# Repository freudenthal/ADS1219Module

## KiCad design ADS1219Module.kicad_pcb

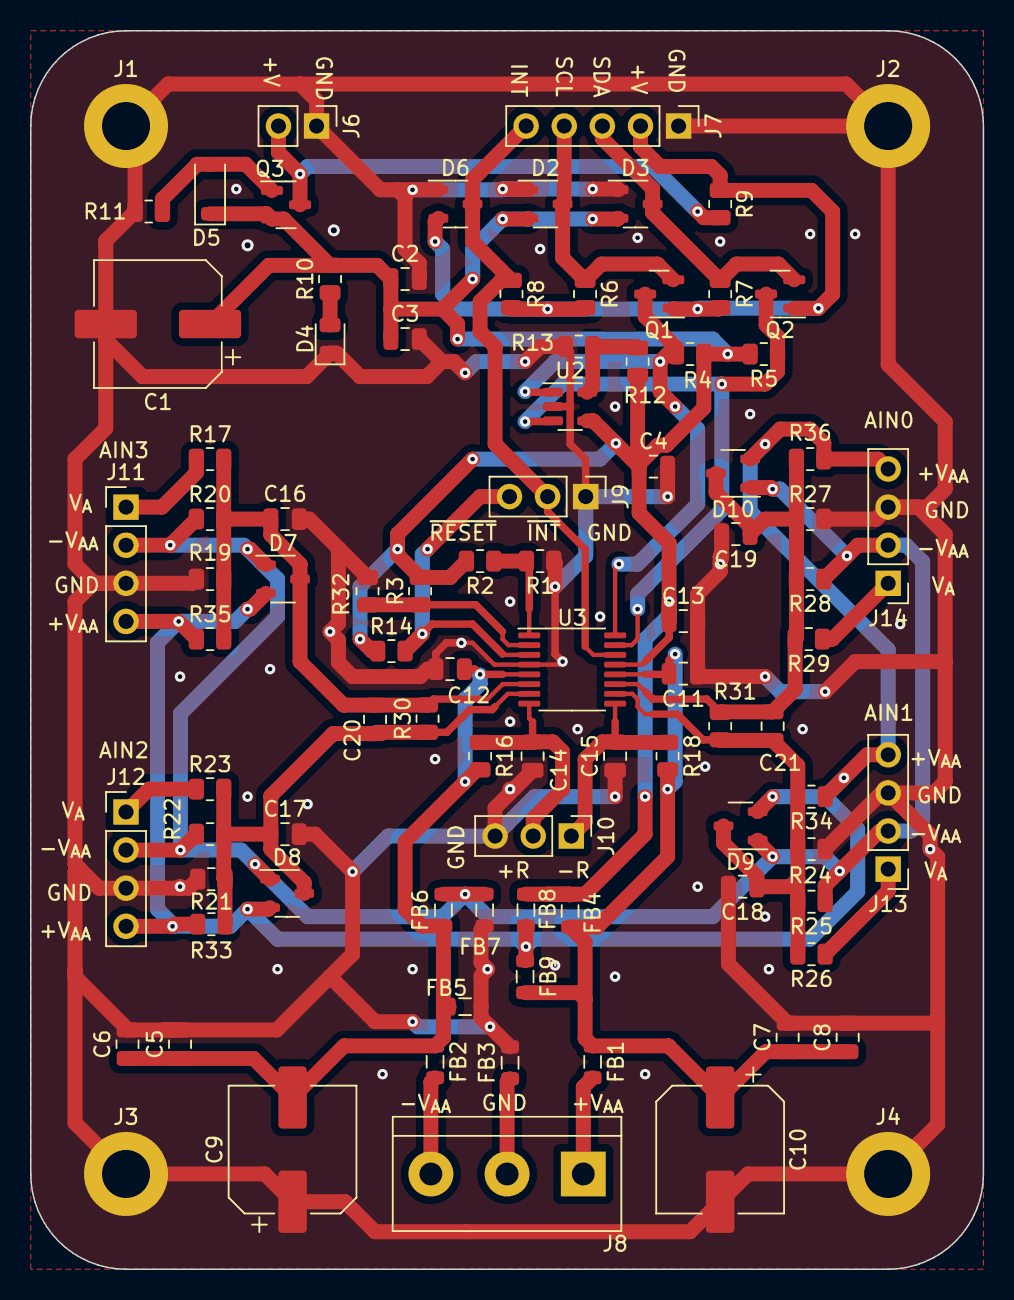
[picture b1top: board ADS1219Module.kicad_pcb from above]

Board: 2 copper layers, 63.5 x 82.5 mm, 92 parts (0 on the bottom side), 32 nets.

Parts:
C1, C9, C10: 100uF; CP_Elec_8x11.9
C2, C6, C8: 10uF; C_0805_2012Metric
C3, C4, C5, C7, C11, C12, C13, C14, C15, C16, C17, C18, C19: 1uF; C_0805_2012Metric
C20, C21: NSF; C_0805_2012Metric
D2, D3, D6, D7, D8, D9, D10: 100V; SOT-23-3
D4: LED; LED_0805_2012Metric
D5: 10V; D_SOD-123
FB1, FB2, FB3: FerriteBead; L_0805_2012Metric
FB4, FB5, FB6, FB7, FB8, FB9: NS_Ferrite; L_0805_2012Metric
J1, J2, J3, J4: M3; MountingHole_3.2mm_M3_DIN965_Pad
J6: 5Vin; PinHeader_1x02_P2.54mm_Vertical
J7: I2C; PinHeader_1x05_P2.54mm_Vertical
J8: VIn; TerminalBlock_bornier-3_P5.08mm
J9: DCON; PinHeader_1x03_P2.54mm_Vertical
J10: REF; PinHeader_1x03_P2.54mm_Vertical
J11, J12, J13, J14: Input; PinHeader_1x04_P2.54mm_Vertical
Q1, Q2: Q_NMOS_GSD; SOT-23
Q3: Q_PMOS_GSD; SOT-23
R1, R16, R18, R32: 0Ω; R_0805_2012Metric
R2, R3, R19, R20, R21, R22, R24, R25, R27, R28, R30, R31, R33, R34, R35, R36: NSΩ; R_0805_2012Metric
R4, R5, R6, R7, R8, R12, R13, R14, R17, R23, R26, R29: 10kΩ; R_0805_2012Metric
R9: NS; R_0805_2012Metric
R10: 500Ω; R_0805_2012Metric
R11: 100kΩ; R_0805_2012Metric
U2: 24FC01T-I/OT; SOT-23-5
U3: ADS1219; TSSOP-16_4.4x5mm_P0.65mm

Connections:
+5V: C1.1, C2.1, C3.1, C4.1, C13.1, D2.2 (K), D3.2 (K), D5.1 (K), FB4.2, FB8.2, Q3.2 (S), R2.2, R3.2, R4.2, R5.2, R10.2, R12.2, R14.1, U2.4 (V_{CC}), U3.13 (DV_{DD})
/ADS1219/A0: R1.2, R2.1, U3.1 (A0)
/ADS1219/A1: R3.1, R32.2, U3.2 (A1)
/ADS1219/AIN0: C19.1, C21.2, D10.3 (A), R27.1, R28.2, R29.2, R31.1, R36.2, U3.11 (AIN0)
/ADS1219/AIN1: C18.1, C21.1, D9.3 (A), R24.1, R25.2, R26.2, R31.2, R34.2, U3.10 (AIN1)
/ADS1219/AIN2: C17.1, C20.2, D8.3 (A), R21.1, R22.2, R23.2, R30.1, R33.2, U3.7 (AIN2)
/ADS1219/AIN3: C16.1, C20.1, D7.3 (A), R17.2, R19.1, R20.2, R30.2, R35.2, U3.6 (AIN3)
/ADS1219/AnalogueConnection/V_{DD}: D7.2 (K), D8.2 (K), D9.2 (K), D10.2 (K), FB8.1, FB9.1, J11.4, J12.4, J13.4, J14.4, R33.1, R34.1, R35.1, R36.1
/ADS1219/AnalogueConnection/V_{SS}: D7.1 (K), D8.1 (K), D9.1 (K), D10.1 (K), FB6.2, FB7.2, J11.2, J12.2, J13.2, J14.2, R20.1, R22.1, R25.1, R28.1
/ADS1219/REFN: C14.2, J10.2, R16.1, U3.8 (REFN)
/ADS1219/REFP: C15.2, J10.1, R18.1, U3.9 (REFP)
/ADS1219/SCL: Q1.3 (D), R4.1, U2.1 (SCL), U3.16 (SCL)
/ADS1219/SDA: Q2.3 (D), R5.1, U2.3 (SDA), U3.15 (SDA)
/ADS1219/~INT: D6.3 (A), J7.5, J9.2, R8.1, U3.14 (~DRDY)
/I2CConnector/VI2C: D6.2 (K), J7.2, Q1.1 (G), Q2.1 (G), R6.2, R7.2, R8.2, R9.1
GND: C1.2, C2.2, C3.2, C4.2, C5.2, C6.2, C7.2, C8.2, C9.1, C10.2, C11.1, C12.2, C13.2, C14.1, C15.1, C16.2, C17.2, C18.2, C19.2, D2.1 (K), D3.1 (K), D4.1 (K), D6.1 (K), FB3.2, FB5.1, FB7.1, J1.1, J2.1, J3.1, J4.1, J6.1, J7.1, J9.1, J10.3, J11.3, J12.3, J13.3, J14.3, R1.1, R11.1, R13.1, R19.2, R21.2, R24.2, R27.2, R32.1, U2.2 (GND), U3.4 (DGND)
unnamed: D2.3 (A), J7.4, Q1.2 (S), R6.1
unnamed: D3.3 (A), J7.3, Q2.2 (S), R7.1
unnamed: D4.2 (A), R10.1
unnamed: D5.2 (A), Q3.1 (G), R11.2
unnamed: J6.2, Q3.3 (D), R9.2
unnamed: FB1.2, J8.1
unnamed: FB3.1, J8.2
unnamed: FB2.2, J8.3
unnamed: J9.3, R14.2, U3.3 (~RESET)
unnamed: J11.1, R17.1
unnamed: J12.1, R23.1
unnamed: J13.1, R26.1
unnamed: J14.1, R29.1
unnamed: R12.1, R13.2, U2.5 (WP)
VAA: C7.1, C8.1, C10.1, C11.2, FB1.1, FB4.1, FB9.2, R18.2, U3.12 (AV_{DD})
VSS: C5.1, C6.1, C9.2, C12.1, FB2.1, FB5.2, FB6.1, R16.2, U3.5 (AGND)
